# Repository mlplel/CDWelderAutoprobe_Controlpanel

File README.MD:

/*
KiCad PC board files for the control

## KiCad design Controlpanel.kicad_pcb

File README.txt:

/*
    Copyright 2022 Michael Jacobs

    Permission is hereby granted, free of charge, to any person obtaining a
    copy of this software and associated documentation files (the "Software"),
    to deal in the Software without restriction, including without limitation
    the rights to use, copy, modify, merge, publish, distribute, sublicense,
    and/or sell copies of the Software, and to permit persons to whom the
    Software is furnished to do so, subject to the following conditions:

    The above copyright notice and this permission notice shall be included
    in all copies or substantial portions of the Software.

    THE SOFTWARE IS PROVIDED "AS IS", WITHOUT WARRANTY OF ANY KIND, EXPRESS
    OR IMPLIED, INCLUDING BUT NOT LIMITED TO THE WARRANTIES OF MERCHANTABILITY,
    FITNESS FOR A PARTICULAR PURPOSE AND NONINFRINGEMENT. IN NO EVENT SHALL THE
    AUTHORS OR COPYRIGHT HOLDERS BE LIABLE FOR ANY CLAIM, DAMAGES OR OTHER
    LIABILITY, WHETHER IN AN ACTION OF CONTRACT, TORT OR OTHERWISE, ARISING
    FROM, OUT OF OR IN CONNECTION WITH THE SOFTWARE OR THE USE OR OTHER
    DEALINGS IN THE SOFTWARE.
*/

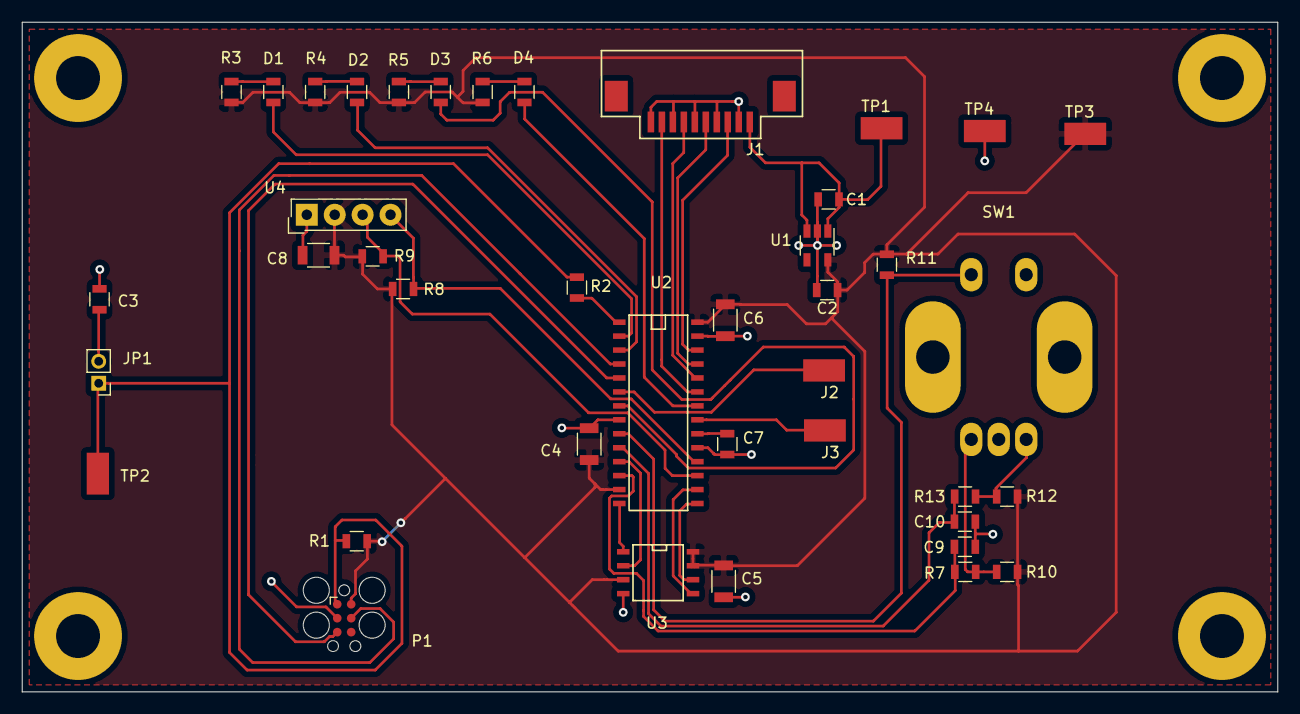
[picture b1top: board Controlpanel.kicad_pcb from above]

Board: 2 copper layers, 114.3 x 61.0 mm, 41 parts (0 on the bottom side), 34 nets.

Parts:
C1, C2: 1u; R_0805
C3: 220n; R_0805
C4, C5, C6, C8: 100n; R_1206
C7: 10u; R_0805
C9, C10: 10n; R_0805
D1, D2, D3, D4: LED; R_0805
J1: Molex_FFC-52207-1033
J2, J3: TP; Keystone-5019
JP1: Jumper_2_Open; Pin_Header_Straight_1x02_Pitch2.00mm
P1: TC2030-MCP; Tag-Connect_TC2030-IDC-FP
R1, R7, R10, R11, R12, R13: 10k; R_0805
R2: 220; R_0805
R3, R4, R5, R6: 470; R_0805
R8, R9: 4.7k; R_0805
SW1: PEC12R-2225F-S0024; PEC12R-4xxxF-Sxxx
TP1, TP2, TP3, TP4: K5019; Keystone-5019
U1: NCP718ASN330T1G; TSOT-23-5
U2: PIC24FJ64GA702; SOIC-28
U3: AT25xxx; SOIC-8-N
U4: i2coled128x64; SL-104-X-XX_1x04

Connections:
+3V3: C2.1, C4.1, C5.1, C6.1, C8.1, P1.2, R1.1, R3.1, R4.1, R5.1, R6.1, R8.1, R9.1, R10.1, R11.1, R12.1, TP3.1, U1.5, U2.13, U2.28, U3.3, U3.7, U3.8, U4.2
/CCS: J1.9, U2.23
/CMISO: J1.5, U2.25
/CMOSI: J1.3, U2.26
/CSCK: J1.7, U2.24
/ENCA: C9.2, R7.1, U2.12
/ENCB: C10.2, R13.1, U2.10
/MCLR: JP1.1, P1.1, R1.2, R2.1, TP2.1
/MCS: U2.14, U3.1
/MMISO: U2.11, U3.2
/MMOSI: U2.16, U3.5
/MSCK: U2.15, U3.6
/PGC: P1.5, U2.5
/PGD: P1.4, U2.4
/SCL: R9.2, U2.17, U4.3
/SDA: R8.2, U2.18, U4.4
/SW: R11.2, SW1.S1, U2.9
/VDC6: C1.1, J1.1, TP1.1, U1.1, U1.3
GND: C1.2, C2.2, C3.2, C4.2, C5.2, C6.2, C7.1, C8.2, C9.1, C10.1, J1.2, J1.4, J1.6, J1.8, J1.10, P1.3, SW1.C, SW1.S2, TP4.1, U1.2, U2.8, U2.19, U2.27, U3.4, U4.1
unnamed: C3.1, JP1.2
unnamed: C7.2, U2.20
unnamed: D1.1, U2.2
unnamed: D1.2, R3.2
unnamed: D2.1, U2.3
unnamed: D2.2, R4.2
unnamed: D3.1, U2.7
unnamed: D3.2, R5.2
unnamed: D4.1, U2.22
unnamed: D4.2, R6.2
unnamed: J2.1, U2.6
unnamed: J3.1, U2.21
unnamed: R2.2, U2.1
unnamed: R7.2, R10.2, SW1.A
unnamed: R12.2, R13.2, SW1.B

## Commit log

2023-01-13 current working version
